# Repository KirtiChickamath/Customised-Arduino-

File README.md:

# Customised-Arduino-
Custom Arduino-compatible PCB project using ATmega328P which includes motor control, 7-segment display, and power supply design
It was developed as part of a course I took from Internshala.

## Project Details

**Project Name:** Customised Arduino

**Software Used:** Eagle 

**Tutorial Reference:**  
This project was developed as part of a course from [Internshala](https://internshala.com/).

## Features

- Powered by a 7805 voltage regulator converting 12V to 5V  
- Controls two small DC motors using the L293D motor driver IC  
- Motor speed can be controlled both via computer commands and manually using a potentiometer on the board  
- Seven-segment display driven by the CD4511BE driver IC, showing numbers 0-9  
- One RGB LED controlled by both the microcontroller and a simple switch on the board

## Project Files

- `Schematic` -- Circuit diagrams  
- `PCB Layout` -- PCB design layout  
- `CAM Outputs` -- Manufacturing files for PCB fabrication  
- `BOM` -- Bill of Materials listing all components   
- `Images` -- Board photos and design previews  
- `Libraries` -- Libraries were provided by mentor

## Images

### Schematic

### PCB Layout

## Credits

This project was developed as part of a course from [Internshala](https://internshala.com/).  

All credit goes to the course instructors and materials that guided this work.

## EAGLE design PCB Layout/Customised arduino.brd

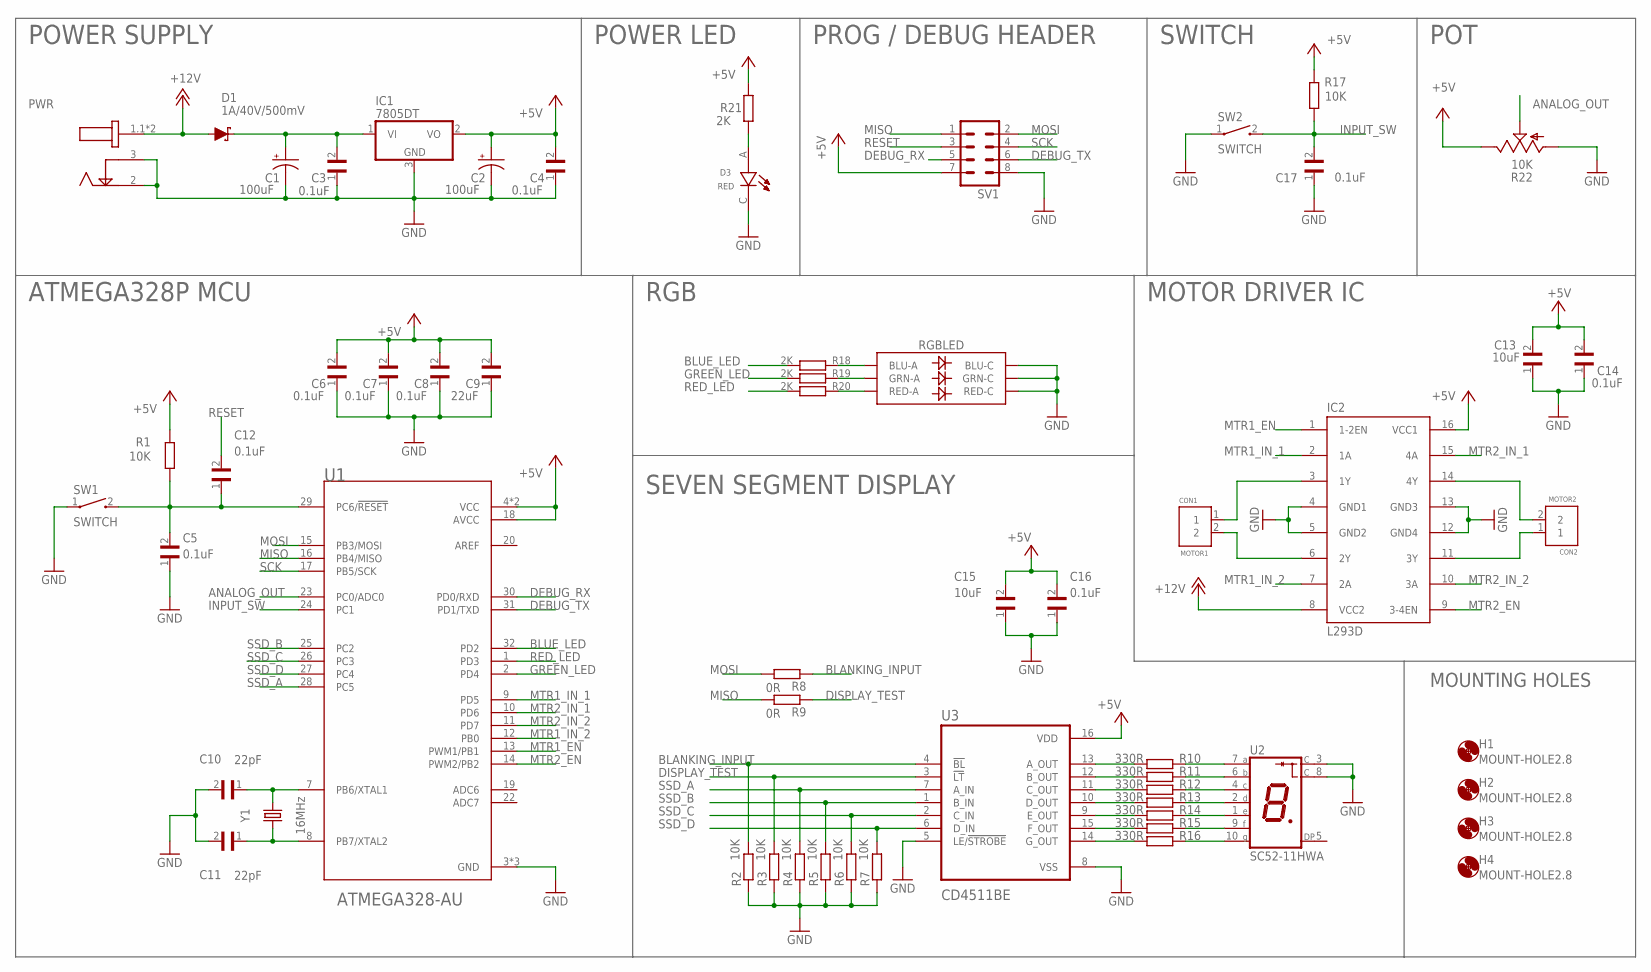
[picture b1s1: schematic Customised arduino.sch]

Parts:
C1, C2: 100uF; CPOL-RADIAL-2.5MM-6.5MM
C3, C4, C5, C6, C7, C8, C12, C14, C16, C17: 0.1uF; C0603
C9: 22uF; C0603
C10, C11: 22pF; C0603
C13, C15: 10uF; C0603
CON1: MOTOR1; CONN_282836-2
CON2: MOTOR2; CONN_282836-2
D1: 1A/40V/500mV; SMA-DIODE
D3: RED; LEDC1608X65N
H1, H2, H3, H4: MOUNT-HOLE2.8; 2,8
IC1: 7805DT; TO252
IC2: L293D; DIL16
PWR: DCJ200-05-A-XX-X_REVA; GCT_DCJ200-05-A-XX-X_REVA
R1, R2, R3, R4, R5, R6, R7, R17: 10K; R0603
R8, R9: 0R; R0603
R10, R11, R12, R13, R14, R15, R16: 330R; R0603
R18, R19, R20, R21: 2K; R0603
R22: 10K; S64W
RGBLED: LED-RGBNO_IC; LED-TRICOLOR-5050
SV1: MA04-2
SW1, SW2: SWITCH; SW_1437566-3
U1: ATMEGA328-AU; QFP80P900X900X120-32N
U2: SC52-11HWA; LED_SC52-11HWA
U3: CD4511BE; DIP794W45P254L1969H508Q16
Y1: 16MHz; HC49US

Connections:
+5V: C2.1 (+), C4.2, C6.2, C7.2, C8.2, C9.2, C13.2, C14.2, C15.2, C16.2, IC1.2 (VO), IC2.16 (VCC1), R1.2, R17.2, R21.2, R22.E, SV1.7, U1.4 (VCC), U1.6 (VCC), U1.18 (AVCC), U3.16 (VDD)
+12V: D1.A, IC2.8 (VCC2), PWR.1.1 (1), PWR.1.2 (1)
ANALOG_OUT: R22.S, U1.23 (PC0/ADC0)
BLANKING_INPUT: R2.2, R8.1, U3.4 (!BL)
BLUE_LED: R18.2, U1.32 (PD2)
DEBUG_RX: SV1.5, U1.30 (PD0/RXD)
DEBUG_TX: SV1.6, U1.31 (PD1/TXD)
DISPLAY_TEST: R3.2, R9.1, U3.3 (!LT)
GND: C1.2 (-), C2.2 (-), C3.1, C4.1, C5.1, C6.1, C7.1, C8.1, C9.1, C10.2, C11.2, C13.1, C14.1, C15.1, C16.1, C17.1, D3.C, IC1.3 (GND), IC2.4 (GND1), IC2.5 (GND2), IC2.12 (GND4), IC2.13 (GND3), PWR.2, PWR.3, R2.1, R3.1, R4.1, R5.1, R6.1, R7.1, R22.A, RGBLED.4 (BLU-C), RGBLED.5 (RED-C), RGBLED.6 (GRN-C), SV1.8, SW1.1, SW2.1, U1.3 (GND), U1.5 (GND), U1.21 (GND), U2.3 (C), U2.8 (C), U3.5 (LE/!STROBE), U3.8 (VSS)
GREEN_LED: R19.2, U1.2 (PD4)
INPUT_SW: C17.2, R17.1, SW2.2, U1.24 (PC1)
MISO: R9.2, SV1.1, U1.16 (PB4/MISO)
MOSI: R8.2, SV1.2, U1.15 (PB3/MOSI)
MTR1_EN: IC2.1 (1-2EN), U1.13 (PWM1/PB1)
MTR1_IN_1: IC2.2 (1A), U1.9 (PD5)
MTR1_IN_2: IC2.7 (2A), U1.12 (PB0)
MTR2_EN: IC2.9 (3-4EN), U1.14 (PWM2/PB2)
MTR2_IN_1: IC2.15 (4A), U1.10 (PD6)
MTR2_IN_2: IC2.10 (3A), U1.11 (PD7)
unnamed: C10.1, U1.7 (PB6/XTAL1), Y1.2
unnamed: C1.1 (+), C3.2, D1.C, IC1.1 (VI)
unnamed: C5.2, C12.1, R1.1, SW1.2, U1.29 (PC6/!RESET)
unnamed: C11.1, U1.8 (PB7/XTAL2), Y1.1
unnamed: CON1.1, IC2.3 (1Y)
unnamed: CON1.2, IC2.6 (2Y)
unnamed: CON2.2, IC2.14 (4Y)
unnamed: CON2.1, IC2.11 (3Y)
unnamed: R10.2, U3.13 (A_OUT)
unnamed: R11.2, U3.12 (B_OUT)
unnamed: R12.2, U3.11 (C_OUT)
unnamed: R13.2, U3.10 (D_OUT)
unnamed: R14.2, U3.9 (E_OUT)
unnamed: R15.2, U3.15 (F_OUT)
unnamed: R16.2, U3.14 (G_OUT)
unnamed: R10.1, U2.7 (A)
unnamed: R11.1, U2.6 (B)
unnamed: R12.1, U2.4 (C)
unnamed: R13.1, U2.2 (D)
unnamed: R14.1, U2.1 (E)
unnamed: R15.1, U2.9 (F)
unnamed: R16.1, U2.10 (G)
unnamed: R18.1, RGBLED.3 (BLU-A)
unnamed: R19.1, RGBLED.1 (GRN-A)
unnamed: R20.1, RGBLED.2 (RED-A)
unnamed: D3.A, R21.1
RED_LED: R20.2, U1.1 (PD3)
RESET: C12.2, SV1.3
SCK: SV1.4, U1.17 (PB5/SCK)
SSD_A: R4.2, U1.28 (PC5), U3.7 (A_IN)
SSD_B: R5.2, U1.25 (PC2), U3.1 (B_IN)
SSD_C: R6.2, U1.26 (PC3), U3.2 (C_IN)
SSD_D: R7.2, U1.27 (PC4), U3.6 (D_IN)

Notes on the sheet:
POWER SUPPLY
PROG / DEBUG HEADER
ATMEGA328P MCU
MOTOR DRIVER IC
SEVEN SEGMENT DISPLAY
SWITCH
RGB
POWER LED
MOUNTING HOLES
POT

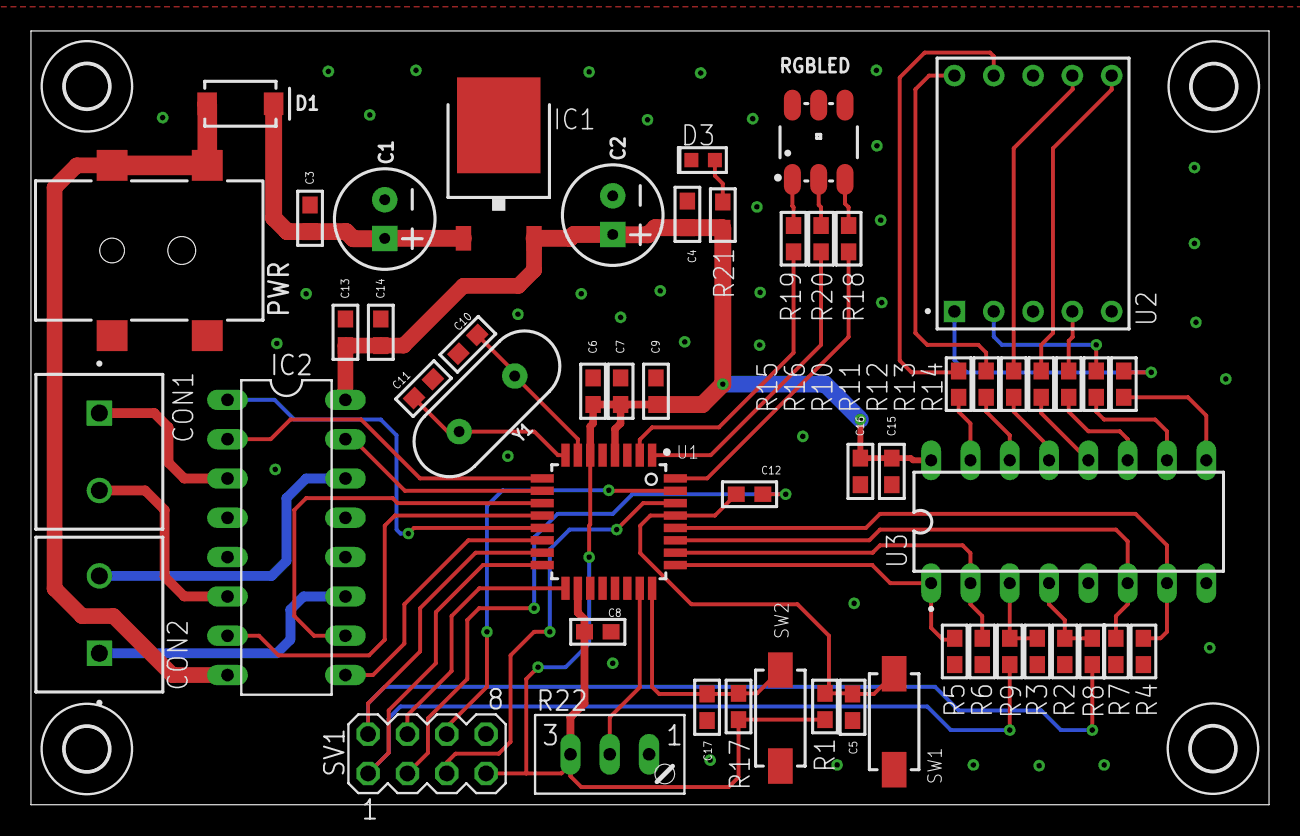
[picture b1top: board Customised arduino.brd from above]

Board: 2 copper layers, 80.0 x 50.0 mm, 58 parts (0 on the bottom side), 52 nets.

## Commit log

2025-05-26 README.md
2025-05-26 Schematic
2025-05-26 Create temp
2025-05-26 Create t
